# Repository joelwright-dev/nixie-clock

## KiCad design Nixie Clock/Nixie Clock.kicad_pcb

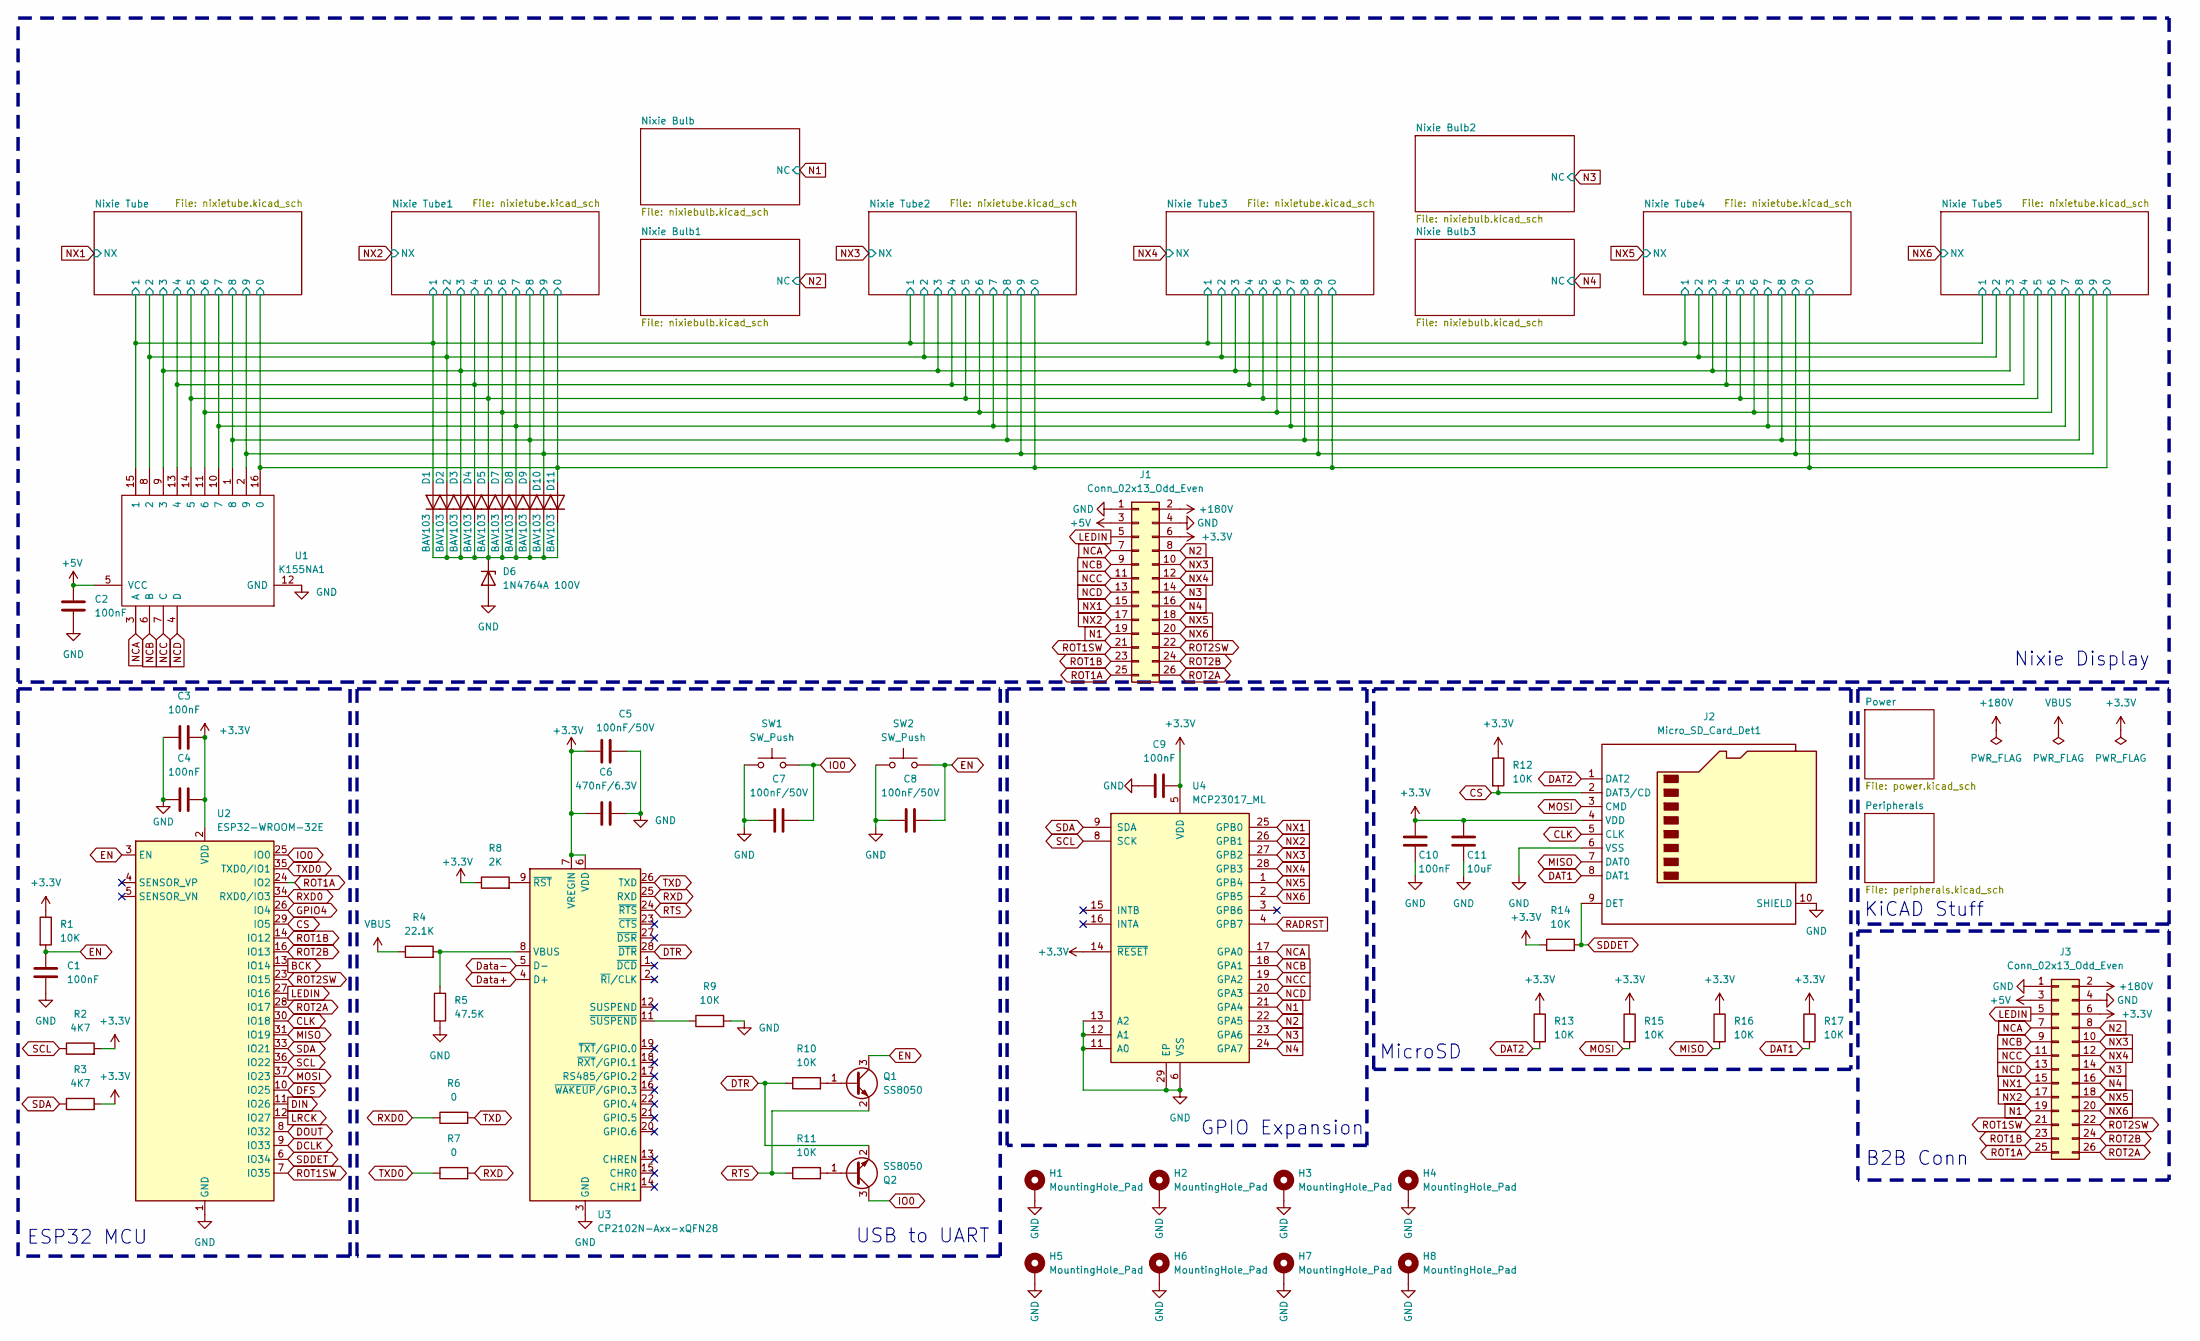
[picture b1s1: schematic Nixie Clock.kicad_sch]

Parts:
C1, C2, C3, C4, C9, C10: 100nF; C_0603_1608Metric
C5, C7, C8: 100nF/50V; C_0603_1608Metric
C6: 470nF/6.3V; C_0603_1608Metric
C11: 10uF; C_0603_1608Metric
D1, D2, D3, D4, D5, D7, D8, D9, D10, D11: BAV103; D_MiniMELF
D6: 1N4764A 100V; D_DO-41_SOD81_P7.62mm_Horizontal
H1, H2, H3, H4, H5, H6, H7, H8: MountingHole_Pad; MountingHole_3.2mm_M3_Pad_Via
J1: Conn_02x13_Odd_Even; PinHeader_2x13_P2.54mm_Vertical
J2: Micro_SD_Card_Det1; microSD_HC_Hirose_DM3AT-SF-PEJM5
J3: Conn_02x13_Odd_Even; PinSocket_2x13_P2.54mm_Vertical
Q1, Q2: SS8050; SOT-23
R1, R9, R10, R11, R12, R13, R14, R15, R16, R17: 10K; R_0603_1608Metric
R2, R3: 4K7; R_0603_1608Metric
R4: 22.1K; R_0603_1608Metric
R5: 47.5K; R_0603_1608Metric
R6, R7: 0; R_0603_1608Metric
R8: 2K; R_0603_1608Metric
SW1, SW2: SW_Push; SW_Push_SPST_NO_Alps_SKRK
U1: K155NA1; DIP-16_W7.62mm
U2: ESP32-WROOM-32E; ESP32-WROOM-32D
U3: CP2102N-Axx-xQFN28; QFN-28-1EP_5x5mm_P0.5mm_EP3.35x3.35mm
U4: MCP23017_ML; QFN-28-1EP_6x6mm_P0.65mm_EP4.25x4.25mm

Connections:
+3.3V: C3.2, C4.2, C5.1, C6.1, C9.2, C10.1, C11.1, J1.6, J2.4 (VDD), J3.6, R1.1, R2.2, R3.2, R8.1, R12.1, R13.1, R14.1, R15.1, R16.1, R17.1, U2.2 (VDD), U3.6 (VDD), U3.7 (VREGIN), U4.5 (VDD), U4.14 (~RESET); also elsewhere on the board
+5V: C2.1, J1.3, J3.3, U1.5 (VCC); also elsewhere on the board
+180V: J1.2, J3.2; also elsewhere on the board
/Nixie Tube/0: D11.2 (A), U1.16 (0); also elsewhere on the board
/Nixie Tube/1: D1.2 (A), U1.15 (1); also elsewhere on the board
/Nixie Tube/2: D2.2 (A), U1.8 (2); also elsewhere on the board
/Nixie Tube/3: D3.2 (A), U1.9 (3); also elsewhere on the board
/Nixie Tube/4: D4.2 (A), U1.13 (4); also elsewhere on the board
/Nixie Tube/5: D5.2 (A), U1.14 (5); also elsewhere on the board
/Nixie Tube/6: D7.2 (A), U1.11 (6); also elsewhere on the board
/Nixie Tube/7: D8.2 (A), U1.10 (7); also elsewhere on the board
/Nixie Tube/8: D9.2 (A), U1.1 (8); also elsewhere on the board
/Nixie Tube/9: D10.2 (A), U1.2 (9); also elsewhere on the board
BCK: U2.13 (IO14); also elsewhere on the board
CLK: J2.5 (CLK), U2.30 (IO18)
CS: J2.2 (DAT3/CD), R12.2, U2.29 (IO5)
DAT1: J2.8 (DAT1), R17.2
DAT2: J2.1 (DAT2), R13.2
DCLK: U2.9 (IO33); also elsewhere on the board
DFS: U2.10 (IO25); also elsewhere on the board
DIN: U2.11 (IO26); also elsewhere on the board
DOUT: U2.8 (IO32); also elsewhere on the board
DTR: Q2.2 (E), R10.1, U3.28 (~DTR)
Data+: U3.4 (D+); also elsewhere on the board
Data-: U3.5 (D-); also elsewhere on the board
EN: C1.1, C8.2, Q1.3 (C), R1.2, SW2.2, U2.3 (EN)
GND: C1.2, C2.2, C3.1, C4.1, C5.2, C6.2, C7.1, C8.1, C9.1, C10.2, C11.2, D6.2 (A), H1.1, H2.1, H3.1, H4.1, H5.1, H6.1, H7.1, H8.1, J1.1, J1.4, J2.6 (VSS), J2.10 (SHIELD), J3.1, J3.4, R5.2, R9.2, SW1.1, SW2.1, U1.12 (GND), U2.1 (GND), U2.15 (GND), U2.38 (GND), U2.39 (GND), U3.3 (GND), U3.29 (GND), U4.6 (VSS), U4.11 (A0), U4.12 (A1), U4.13 (A2), U4.29 (EP); also elsewhere on the board
GPIO4: U2.26 (IO4); also elsewhere on the board
IO0: C7.2, Q2.3 (C), SW1.2, U2.25 (IO0)
LEDIN: J1.5, J3.5, U2.27 (IO16); also elsewhere on the board
LRCK: U2.12 (IO27); also elsewhere on the board
MISO: J2.7 (DAT0), R16.2, U2.31 (IO19)
MOSI: J2.3 (CMD), R15.2, U2.37 (IO23)
N1: J1.19, J3.19, U4.21 (GPA4); also elsewhere on the board
N2: J1.8, J3.8, U4.22 (GPA5); also elsewhere on the board
N3: J1.14, J3.14, U4.23 (GPA6); also elsewhere on the board
N4: J1.16, J3.16, U4.24 (GPA7); also elsewhere on the board
NCA: J1.7, J3.7, U1.3 (A), U4.17 (GPA0)
NCB: J1.9, J3.9, U1.6 (B), U4.18 (GPA1)
NCC: J1.11, J3.11, U1.7 (C), U4.19 (GPA2)
NCD: J1.13, J3.13, U1.4 (D), U4.20 (GPA3)
NX1: J1.15, J3.15, U4.25 (GPB0); also elsewhere on the board
NX2: J1.17, J3.17, U4.26 (GPB1); also elsewhere on the board
NX3: J1.10, J3.10, U4.27 (GPB2); also elsewhere on the board
NX4: J1.12, J3.12, U4.28 (GPB3); also elsewhere on the board
NX5: J1.18, J3.18, U4.1 (GPB4); also elsewhere on the board
NX6: J1.20, J3.20, U4.2 (GPB5); also elsewhere on the board
unnamed: D1.1 (K), D2.1 (K), D3.1 (K), D4.1 (K), D5.1 (K), D6.1 (K), D7.1 (K), D8.1 (K), D9.1 (K), D10.1 (K), D11.1 (K)
unnamed: Q1.1 (B), R10.2
unnamed: Q2.1 (B), R11.2
unnamed: R4.2, R5.1, U3.8 (VBUS)
unnamed: R8.2, U3.9 (~RST)
unnamed: R9.1, U3.11 (~SUSPEND)
RADRST: U4.4 (GPB7); also elsewhere on the board
ROT1A: J1.25, J3.25, U2.24 (IO2); also elsewhere on the board
ROT1B: J1.23, J3.23, U2.14 (IO12); also elsewhere on the board
ROT1SW: J1.21, J3.21, U2.7 (IO35); also elsewhere on the board
ROT2A: J1.26, J3.26, U2.28 (IO17); also elsewhere on the board
ROT2B: J1.24, J3.24, U2.16 (IO13); also elsewhere on the board
ROT2SW: J1.22, J3.22, U2.23 (IO15); also elsewhere on the board
RTS: Q1.2 (E), R11.1, U3.24 (~RTS)
RXD: R7.2, U3.25 (RXD)
RXD0: R6.1, U2.34 (RXD0/IO3)
SCL: R2.1, U2.36 (IO22), U4.8 (SCK); also elsewhere on the board
SDA: R3.1, U2.33 (IO21), U4.9 (SDA); also elsewhere on the board
SDDET: J2.9 (DET), R14.2, U2.6 (IO34)
TXD: R6.2, U3.26 (TXD)
TXD0: R7.1, U2.35 (TXD0/IO1)
VBUS: R4.1; also elsewhere on the board

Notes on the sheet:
MicroSD
KiCAD Stuff
USB to UART
Nixie Display
B2B Conn
ESP32 MCU
GPIO Expansion

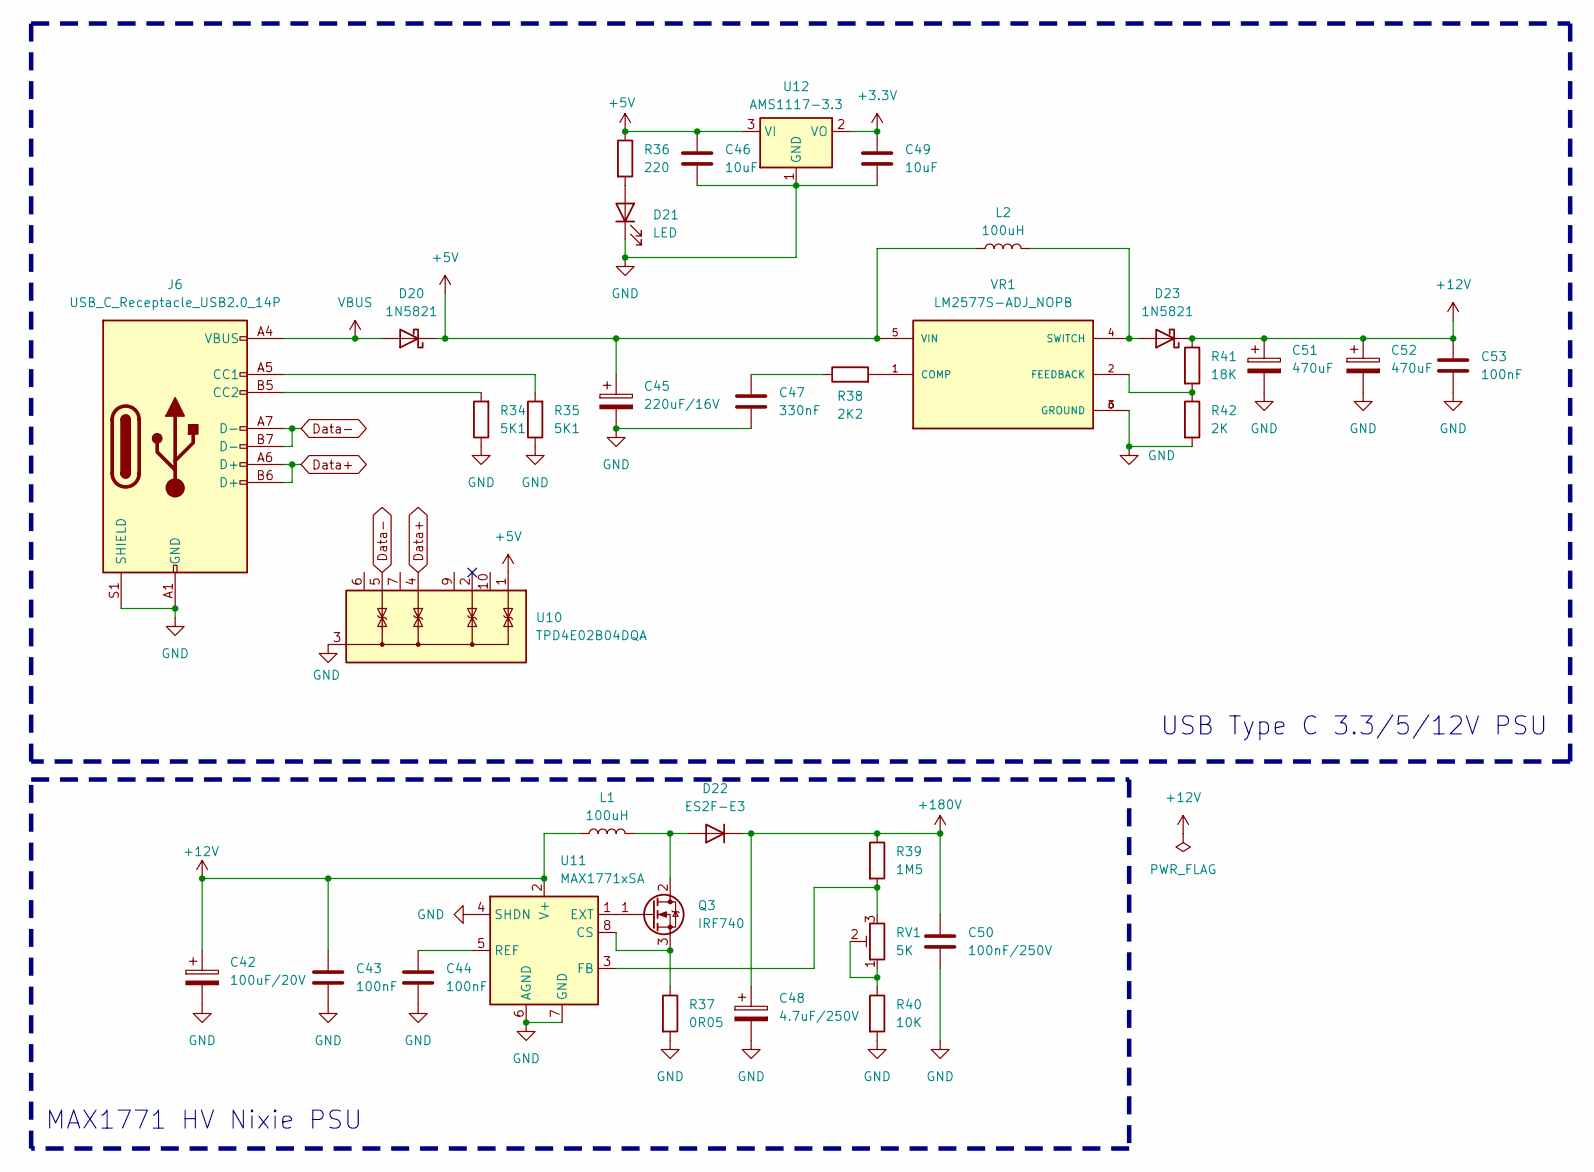
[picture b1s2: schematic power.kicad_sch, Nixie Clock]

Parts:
C42: 100uF/20V; CP_Elec_6.3x7.7
C43, C44, C53: 100nF; C_0603_1608Metric
C45: 220uF/16V; CP_Elec_10x10
C46, C49: 10uF; C_0603_1608Metric
C47: 330nF; C_0603_1608Metric
C48: 4.7uF/250V; CP_Elec_8x10.5
C50: 100nF/250V; C_0603_1608Metric
C51, C52: 470uF; CP_Elec_10x10.5
D20, D23: 1N5821; D_DO-201AD_P12.70mm_Horizontal
D21: LED; LED_0201_0603Metric
D22: ES2F-E3; D_SMB
J6: USB_C_Receptacle_USB2.0_14P; USB_C_Receptacle_G-Switch_GT-USB-7051x
L1, L2: 100uH; L_12x12mm_H8mm
Q3: IRF740; TO-220-3_Horizontal_TabUp
R34, R35: 5K1; R_0603_1608Metric
R36: 220; R_0603_1608Metric
R37: 0R05; R_0603_1608Metric
R38: 2K2; R_0603_1608Metric
R39: 1M5; R_0603_1608Metric
R40: 10K; R_0603_1608Metric
R41: 18K; R_0603_1608Metric
R42: 2K; R_0603_1608Metric
RV1: 5K; Potentiometer_Bourns_3296W_Vertical
U10: TPD4E02B04DQA; USON-10_2.5x1.0mm_P0.5mm
U11: MAX1771xSA; SO-8_3.9x4.9mm_P1.27mm
U12: AMS1117-3.3; SOT-223-3_TabPin2
VR1: LM2577S-ADJ_NOPB; VREG_LM2577S-ADJ_NOPB; PARTREV D

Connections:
+3.3V: C49.1, U12.2 (VO); also elsewhere on the board
+5V: C45.1, C46.1, D20.1 (K), L2.1, R36.1, U10.1 (IO1), U12.3 (VI), VR1.5 (VIN); also elsewhere on the board
+12V: C42.1, C43.1, C51.1, C52.1, C53.1, D23.1 (K), L1.1, R41.1, U11.2 (V+)
+180V: C48.1, C50.1, D22.1 (K), R39.1; also elsewhere on the board
Data+: J6.A6 (D+), J6.B6 (D+), U10.4 (IO3); also elsewhere on the board
Data-: J6.A7 (D-), J6.B7 (D-), U10.5 (IO4); also elsewhere on the board
GND: C42.2, C43.2, C44.2, C45.2, C46.2, C47.2, C48.2, C49.2, C50.2, C51.2, C52.2, C53.2, D21.1 (K), J6.A1 (GND), J6.A12 (GND), J6.B1 (GND), J6.B12 (GND), J6.S1 (SHIELD), R34.1, R35.1, R37.2, R40.2, R42.2, U10.3 (G), U10.8 (G), U11.4 (SHDN), U11.6 (AGND), U11.7 (GND), U12.1 (GND), VR1.3 (GROUND), VR1.6 (GROUND); also elsewhere on the board
unnamed: C47.1, R38.1
unnamed: D21.2 (A), R36.2
unnamed: D22.2 (A), L1.2, Q3.2 (D)
unnamed: D23.2 (A), L2.2, VR1.4 (SWITCH)
unnamed: J6.A5 (CC1), R35.2
unnamed: J6.B5 (CC2), R34.2
unnamed: Q3.1 (G), U11.1 (EXT)
unnamed: Q3.3 (S), R37.1, U11.8 (CS)
unnamed: R40.1, RV1.1, RV1.2
unnamed: R39.2, RV1.3, U11.3 (FB)
unnamed: C44.1, U11.5 (REF)
unnamed: R38.2, VR1.1 (COMP)
unnamed: R41.2, R42.1, VR1.2 (FEEDBACK)
VBUS: D20.2 (A), J6.A4 (VBUS), J6.A9 (VBUS), J6.B4 (VBUS), J6.B9 (VBUS); also elsewhere on the board

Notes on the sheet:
USB Type C 3.3/5/12V PSU
MAX1771 HV Nixie PSU

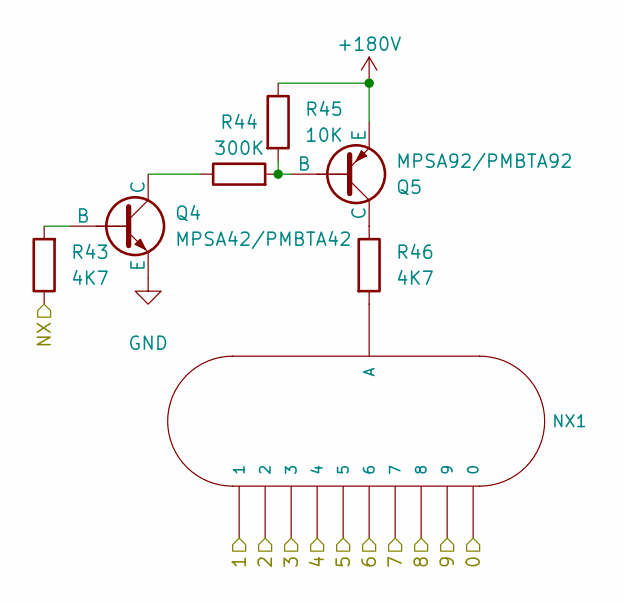
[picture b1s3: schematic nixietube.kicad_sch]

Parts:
NX1: IN-12A; IN-12-DSUB-NOHOLE
Q4: MPSA42/PMBTA42; SOT-23
Q5: MPSA92/PMBTA92; SOT-23
R43, R46: 4K7; R_0603_1608Metric
R44: 300K; R_0603_1608Metric
R45: 10K; R_0603_1608Metric

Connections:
+180V: Q5.3 (E), R45.1; also elsewhere on the board
/Nixie Tube/0: NX1.0; also elsewhere on the board
/Nixie Tube/1: NX1.1; also elsewhere on the board
/Nixie Tube/2: NX1.2; also elsewhere on the board
/Nixie Tube/3: NX1.3; also elsewhere on the board
/Nixie Tube/4: NX1.4; also elsewhere on the board
/Nixie Tube/5: NX1.5; also elsewhere on the board
/Nixie Tube/6: NX1.6; also elsewhere on the board
/Nixie Tube/7: NX1.7; also elsewhere on the board
/Nixie Tube/8: NX1.8; also elsewhere on the board
/Nixie Tube/9: NX1.9; also elsewhere on the board
GND: Q4.3 (E); also elsewhere on the board
NX1: R43.1; also elsewhere on the board
unnamed: NX1.A, R46.2
unnamed: Q4.2 (B), R43.2
unnamed: Q4.1 (C), R44.1
unnamed: Q5.2 (B), R44.2, R45.2
unnamed: Q5.1 (C), R46.1

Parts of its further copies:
NX2, NX3, NX4, NX5, NX6: IN-12A; IN-12-DSUB-NOHOLE
Q6, Q8, Q10, Q12, Q14: MPSA42/PMBTA42; SOT-23
Q7, Q9, Q11, Q13, Q15: MPSA92/PMBTA92; SOT-23
R47, R50, R51, R54, R55, R58, R59, R62, R63, R66: 4K7; R_0603_1608Metric
R48, R52, R56, R60, R64: 300K; R_0603_1608Metric
R49, R53, R57, R61, R65: 10K; R_0603_1608Metric

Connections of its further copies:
+180V: Q7.3 (E), Q9.3 (E), Q11.3 (E), Q13.3 (E), Q15.3 (E), R49.1, R53.1, R57.1, R61.1, R65.1; also elsewhere on the board
/Nixie Tube/0: NX2.0, NX3.0, NX4.0, NX5.0, NX6.0; also elsewhere on the board
/Nixie Tube/1: NX2.1, NX3.1, NX4.1, NX5.1, NX6.1; also elsewhere on the board
/Nixie Tube/2: NX2.2, NX3.2, NX4.2, NX5.2, NX6.2; also elsewhere on the board
/Nixie Tube/3: NX2.3, NX3.3, NX4.3, NX5.3, NX6.3; also elsewhere on the board
/Nixie Tube/4: NX2.4, NX3.4, NX4.4, NX5.4, NX6.4; also elsewhere on the board
/Nixie Tube/5: NX2.5, NX3.5, NX4.5, NX5.5, NX6.5; also elsewhere on the board
/Nixie Tube/6: NX2.6, NX3.6, NX4.6, NX5.6, NX6.6; also elsewhere on the board
/Nixie Tube/7: NX2.7, NX3.7, NX4.7, NX5.7, NX6.7; also elsewhere on the board
/Nixie Tube/8: NX2.8, NX3.8, NX4.8, NX5.8, NX6.8; also elsewhere on the board
/Nixie Tube/9: NX2.9, NX3.9, NX4.9, NX5.9, NX6.9; also elsewhere on the board
GND: Q6.3 (E), Q8.3 (E), Q10.3 (E), Q12.3 (E), Q14.3 (E); also elsewhere on the board
NX2: R47.1; also elsewhere on the board
NX3: R51.1; also elsewhere on the board
NX4: R55.1; also elsewhere on the board
NX5: R59.1; also elsewhere on the board
NX6: R63.1; also elsewhere on the board
unnamed: NX2.A, R50.2
unnamed: NX3.A, R54.2
unnamed: NX4.A, R58.2
unnamed: NX5.A, R62.2
unnamed: NX6.A, R66.2
unnamed: Q6.2 (B), R47.2
unnamed: Q6.1 (C), R48.1
unnamed: Q7.2 (B), R48.2, R49.2
unnamed: Q7.1 (C), R50.1
unnamed: Q8.2 (B), R51.2
unnamed: Q8.1 (C), R52.1
unnamed: Q9.2 (B), R52.2, R53.2
unnamed: Q9.1 (C), R54.1
unnamed: Q10.2 (B), R55.2
unnamed: Q10.1 (C), R56.1
unnamed: Q11.2 (B), R56.2, R57.2
unnamed: Q11.1 (C), R58.1
unnamed: Q12.2 (B), R59.2
unnamed: Q12.1 (C), R60.1
unnamed: Q13.2 (B), R60.2, R61.2
unnamed: Q13.1 (C), R62.1
unnamed: Q14.2 (B), R63.2
unnamed: Q14.1 (C), R64.1
unnamed: Q15.2 (B), R64.2, R65.2
unnamed: Q15.1 (C), R66.1

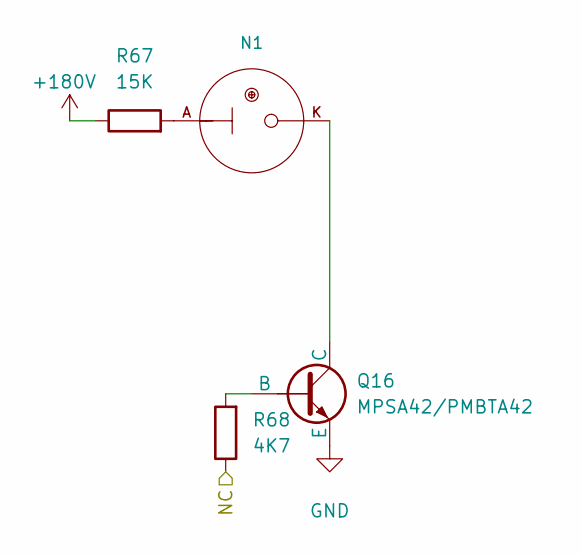
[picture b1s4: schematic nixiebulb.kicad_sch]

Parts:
N1: IN-6
Q16: MPSA42/PMBTA42; SOT-23
R67: 15K; R_0603_1608Metric
R68: 4K7; R_0603_1608Metric

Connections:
+180V: R67.1; also elsewhere on the board
GND: Q16.3 (E); also elsewhere on the board
N1: R68.1; also elsewhere on the board
unnamed: N1.A, R67.2
unnamed: Q16.2 (B), R68.2
unnamed: N1.K, Q16.1 (C)

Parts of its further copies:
N2, N3, N4: IN-6
Q17, Q18, Q19: MPSA42/PMBTA42; SOT-23
R69, R71, R73: 15K; R_0603_1608Metric
R70, R72, R74: 4K7; R_0603_1608Metric

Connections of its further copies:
+180V: R69.1, R71.1, R73.1; also elsewhere on the board
GND: Q17.3 (E), Q18.3 (E), Q19.3 (E); also elsewhere on the board
N2: R70.1; also elsewhere on the board
N3: R72.1; also elsewhere on the board
N4: R74.1; also elsewhere on the board
unnamed: N2.A, R69.2
unnamed: N3.A, R71.2
unnamed: N4.A, R73.2
unnamed: Q17.2 (B), R70.2
unnamed: N2.K, Q17.1 (C)
unnamed: Q18.2 (B), R72.2
unnamed: N3.K, Q18.1 (C)
unnamed: Q19.2 (B), R74.2
unnamed: N4.K, Q19.1 (C)

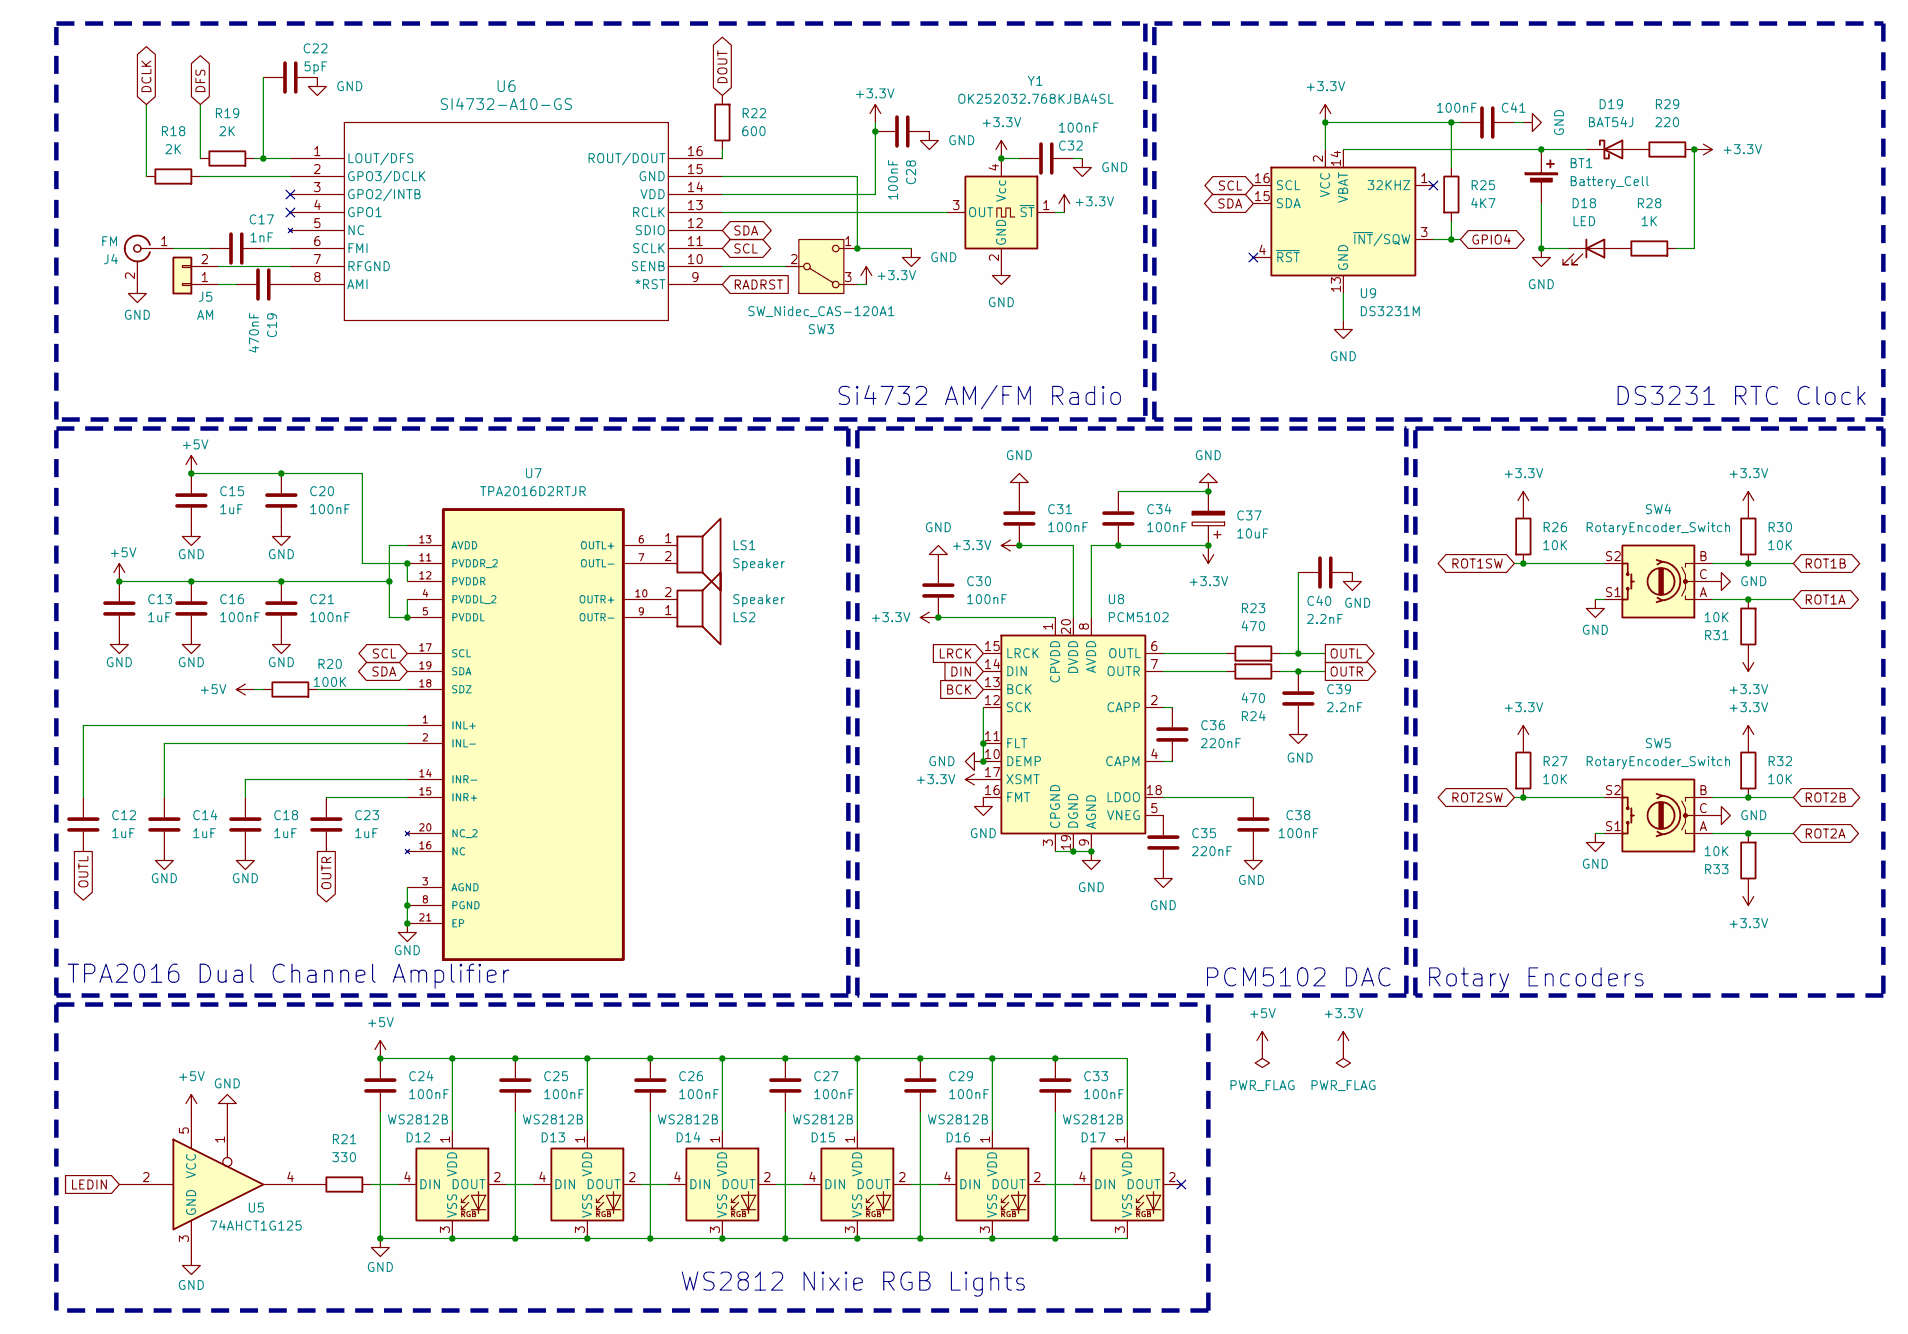
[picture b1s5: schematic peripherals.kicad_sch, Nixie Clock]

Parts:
BT1: Battery_Cell; BatteryHolder_Keystone_1060_1x2032
C12, C13, C14, C15, C18, C23: 1uF; C_0603_1608Metric
C16, C20, C21, C24, C25, C26, C27, C28, C29, C30, C31, C32, C33, C34, C38, C41: 100nF; C_0603_1608Metric
C17: 1nF; C_0603_1608Metric
C19: 470nF; C_0603_1608Metric
C22: 5pF; C_0603_1608Metric
C35, C36: 220nF; C_0603_1608Metric
C37: 10uF; C_0603_1608Metric
C39, C40: 2.2nF; C_0603_1608Metric
D12, D13, D14, D15, D16, D17: WS2812B; LED_WS2812B_PLCC4_5.0x5.0mm_P3.2mm
D18: LED; LED_0201_0603Metric
D19: BAT54J; D_SOD-323F
J4: FM; SMA_Amphenol_901-144_Vertical
J5: AM; JST_XH_B2B-XH-A_1x02_P2.50mm_Vertical
LS1, LS2: Speaker; JST_XH_B2B-XH-A_1x02_P2.50mm_Vertical
R18, R19: 2K; R_0603_1608Metric
R20: 100K; R_0603_1608Metric
R21: 330; R_0603_1608Metric
R22: 600; R_0603_1608Metric
R23, R24: 470; R_0603_1608Metric
R25: 4K7; R_0603_1608Metric
R26, R27, R30, R31, R32, R33: 10K; R_0603_1608Metric
R28: 1K; R_0603_1608Metric
R29: 220; R_0603_1608Metric
SW3: SW_Nidec_CAS-120A1; Nidec_Copal_CAS-120A
SW4, SW5: RotaryEncoder_Switch; RotaryEncoder_Alps_EC11E-Switch_Vertical_H20mm
U5: 74AHCT1G125; SOT-23-5
U6: SI4732-A10-GS; SOIC_A10-GS_SIL
U7: TPA2016D2RTJR; QFN50P400X400X80-21N; MPN TPA2016D2RTJR
U8: PCM5102; TSSOP-20_4.4x6.5mm_P0.65mm
U9: DS3231M; SOIC-16W_7.5x10.3mm_P1.27mm
Y1: OK252032.768KJBA4SL; Oscillator_SMD_SeikoEpson_SG210-4Pin_2.5x2.0mm

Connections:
+3.3V: C28.2, C30.1, C31.1, C32.2, C34.1, C37.1, C41.2, R25.1, R26.1, R27.1, R28.2, R29.2, R30.1, R31.1, R32.1, R33.1, SW3.3 (A), U6.14 (VDD), U8.1 (CPVDD), U8.8 (AVDD), U8.17 (XSMT), U8.20 (DVDD), U9.2 (VCC), Y1.1 (~ST), Y1.4 (Vcc); also elsewhere on the board
+5V: C13.2, C15.2, C16.2, C20.2, C21.2, C24.1, C25.1, C26.1, C27.1, C29.1, C33.1, D12.1 (VDD), D13.1 (VDD), D14.1 (VDD), D15.1 (VDD), D16.1 (VDD), D17.1 (VDD), R20.1, U5.5 (VCC), U7.4 (PVDDL_2), U7.5 (PVDDL), U7.11 (PVDDR_2), U7.12 (PVDDR), U7.13 (AVDD); also elsewhere on the board
BCK: U8.13 (BCK); also elsewhere on the board
DCLK: R18.1; also elsewhere on the board
DFS: R19.1; also elsewhere on the board
DIN: U8.14 (DIN); also elsewhere on the board
DOUT: R22.2; also elsewhere on the board
GND: BT1.2 (-), C13.1, C14.1, C15.1, C16.1, C18.1, C20.1, C21.1, C22.1, C24.2, C25.2, C26.2, C27.2, C28.1, C29.2, C30.2, C31.2, C32.1, C33.2, C34.2, C35.2, C37.2, C38.2, C39.2, C40.1, C41.1, D12.3 (VSS), D13.3 (VSS), D14.3 (VSS), D15.3 (VSS), D16.3 (VSS), D17.3 (VSS), D18.1 (K), J4.2 (Ext), SW3.1 (C), SW4.C, SW4.S1, SW5.C, SW5.S1, U5.1, U5.3 (GND), U6.15 (GND), U7.3 (AGND), U7.8 (PGND), U7.21 (EP), U8.3 (CPGND), U8.9 (AGND), U8.10 (DEMP), U8.11 (FLT), U8.12 (SCK), U8.16 (FMT), U8.19 (DGND), U9.5 (GND), U9.6 (GND), U9.7 (GND), U9.8 (GND), U9.9 (GND), U9.10 (GND), U9.11 (GND), U9.12 (GND), U9.13 (GND), Y1.2 (GND); also elsewhere on the board
GPIO4: R25.2, U9.3 (~INT/SQW); also elsewhere on the board
LEDIN: U5.2; also elsewhere on the board
LRCK: U8.15 (LRCK); also elsewhere on the board
unnamed: BT1.1 (+), D19.1 (K), U9.14 (VBAT)
unnamed: D12.4 (DIN), R21.2
unnamed: D12.2 (DOUT), D13.4 (DIN)
unnamed: D13.2 (DOUT), D14.4 (DIN)
unnamed: D14.2 (DOUT), D15.4 (DIN)
unnamed: D15.2 (DOUT), D16.4 (DIN)
unnamed: D16.2 (DOUT), D17.4 (DIN)
unnamed: D18.2 (A), R28.1
unnamed: D19.2 (A), R29.1
unnamed: C17.2, J4.1 (In)
unnamed: C19.2, J5.1
unnamed: J5.2, U6.7 (RFGND)
unnamed: R21.1, U5.4
unnamed: SW3.2 (B), U6.10 (SENB)
unnamed: C19.1, U6.8 (AMI)
unnamed: C17.1, U6.6 (FMI)
unnamed: R18.2, U6.2 (GPO3/DCLK)
unnamed: C22.2, R19.2, U6.1 (LOUT/DFS)
unnamed: U6.13 (RCLK), Y1.3 (OUT)
unnamed: R22.1, U6.16 (ROUT/DOUT)
unnamed: C12.2, U7.1 (INL+)
unnamed: C14.2, U7.2 (INL-)
unnamed: C23.2, U7.15 (INR+)
unnamed: C18.2, U7.14 (INR-)
unnamed: LS1.1, U7.6 (OUTL+)
unnamed: LS1.2, U7.7 (OUTL-)
unnamed: LS2.2, U7.10 (OUTR+)
unnamed: LS2.1, U7.9 (OUTR-)
unnamed: R20.2, U7.18 (SDZ)
unnamed: C36.2, U8.4 (CAPM)
unnamed: C36.1, U8.2 (CAPP)
unnamed: C38.1, U8.18 (LDOO)
unnamed: R23.1, U8.6 (OUTL)
unnamed: R24.2, U8.7 (OUTR)
unnamed: C35.1, U8.5 (VNEG)
OUTL: C12.1, C40.2, R23.2
OUTR: C23.1, C39.1, R24.1
RADRST: U6.9 (*RST); also elsewhere on the board
ROT1A: R31.2, SW4.A; also elsewhere on the board
ROT1B: R30.2, SW4.B; also elsewhere on the board
ROT1SW: R26.2, SW4.S2; also elsewhere on the board
ROT2A: R33.2, SW5.A; also elsewhere on the board
ROT2B: R32.2, SW5.B; also elsewhere on the board
ROT2SW: R27.2, SW5.S2; also elsewhere on the board
SCL: U6.11 (SCLK), U7.17 (SCL), U9.16 (SCL); also elsewhere on the board
SDA: U6.12 (SDIO), U7.19 (SDA), U9.15 (SDA); also elsewhere on the board

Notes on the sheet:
Si4732 AM/FM Radio
TPA2016 Dual Channel Amplifier
PCM5102 DAC
DS3231 RTC Clock
WS2812 Nixie RGB Lights
Rotary Encoders

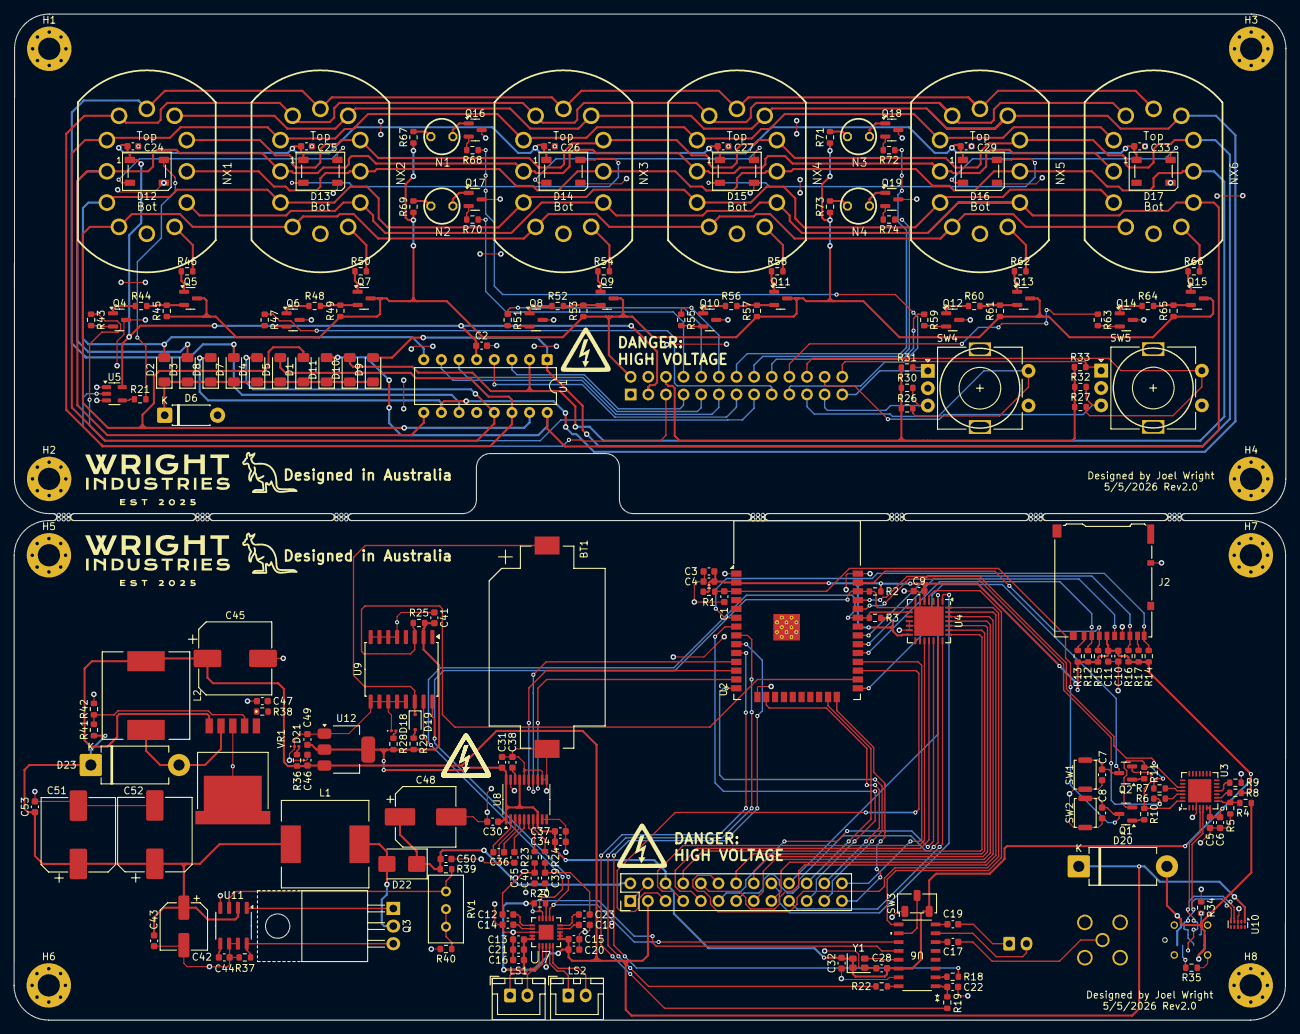
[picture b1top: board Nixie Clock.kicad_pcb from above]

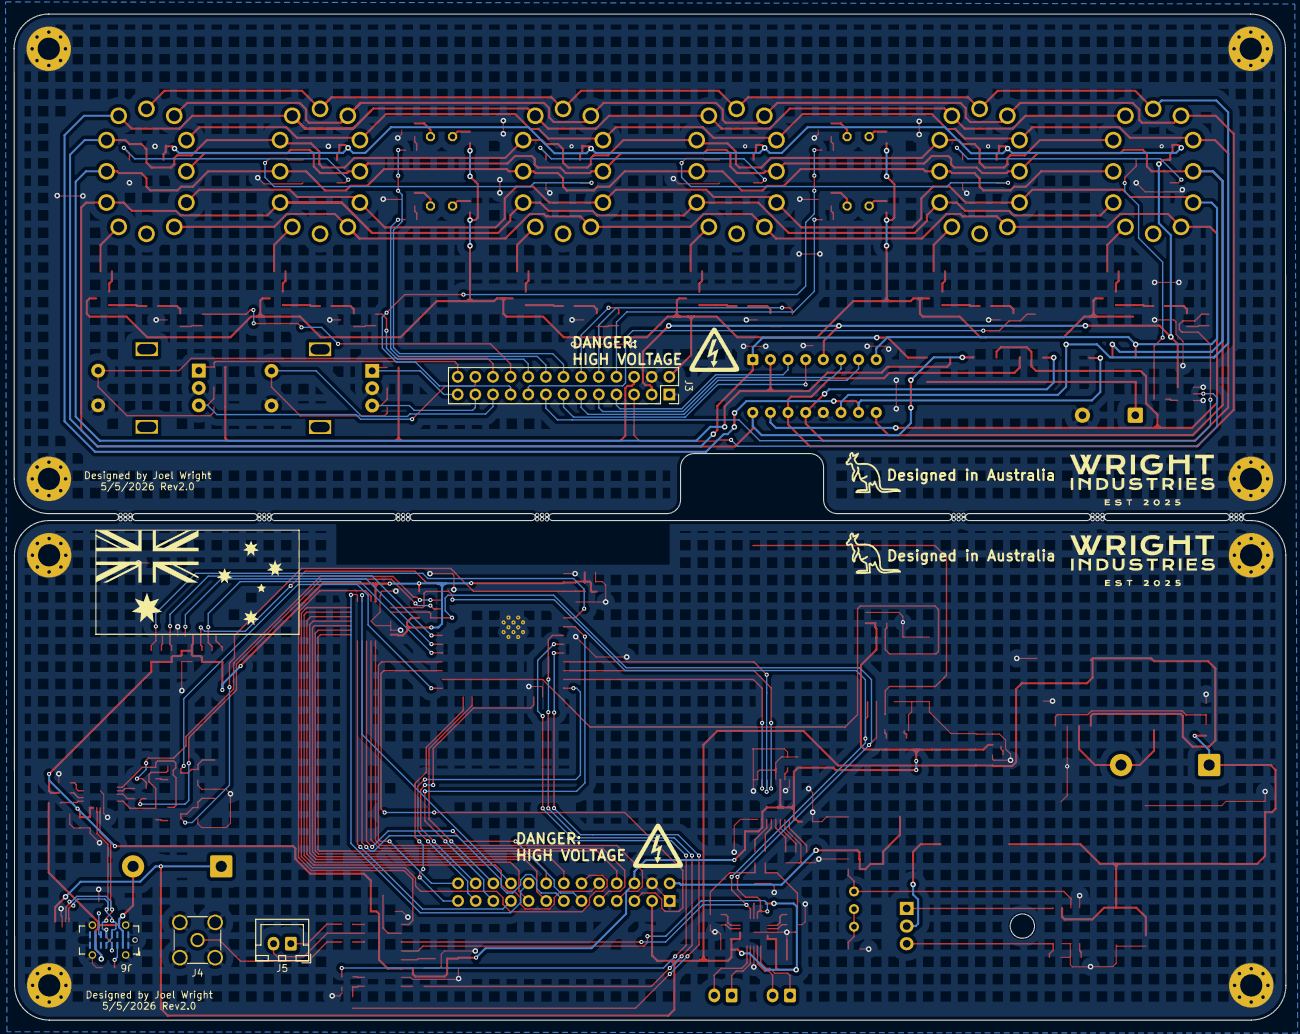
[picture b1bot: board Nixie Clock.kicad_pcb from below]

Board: 2 copper layers, 183.2 x 144.9 mm, 225 parts (4 on the bottom side), 162 nets.

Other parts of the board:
mouse-bite-1mm-3mm, mouse-bite-1mm-3mm#2, mouse-bite-1mm-3mm#3, mouse-bite-1mm-3mm#4, mouse-bite-1mm-3mm#5, mouse-bite-1mm-3mm#6, mouse-bite-1mm-3mm#7: VAL**; mouse-bite-1mm-3mm

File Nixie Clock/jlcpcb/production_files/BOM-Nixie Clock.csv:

Comment,Designator,Footprint,LCSC,Quantity
0,"R6,R7",R_0603_1608Metric,C21189,2
0R05,R37,R_0603_1608Metric,C14709,1
100K,R20,R_0603_1608Metric,C25803,1
100nF,"C1,C10,C16,C2,C20,C21,C24,C25,C26,C27,C28,C29,C3,C30,C31,C32,C33,C34,C38,C4,C41,C43,C44,C53,C9",C_0603_1608Metric,C14663,25
100nF/250V,C50,C_1206_3216Metric,C22374889,1
100nF/50V,"C5,C7,C8",C_0603_1608Metric,C14663,3
100uF/20V,C42,CP_Elec_6.3x7.7,C3338,1
100uH,"L1,L2",L_12x12mm_H8mm,C6463690,2
10K,"R1,R10,R11,R12,R13,R14,R15,R16,R17,R26,R27,R30,R31,R32,R33,R40,R45,R49,R53,R57,R61,R65,R9",R_0603_1608Metric,C25804,23
10uF,"C11,C37,C46,C49",C_0603_1608Metric,C96446,4
15K,"R67,R69,R71,R73",R_0603_1608Metric,C22809,4
18K,R41,R_0603_1608Metric,C25810,1
1K,R28,R_0603_1608Metric,C21190,1
1M5,R39,R_0603_1608Metric,C4172,1
1N4764A 100V,D6,D_DO-41_SOD81_P7.62mm_Horizontal,C2764506,1
1N5821,"D20,D23",D_DO-201AD_P12.70mm_Horizontal,C9119,2
1nF,C17,C_0603_1608Metric,C1588,1
1uF,"C12,C13,C14,C15,C18,C23",C_0603_1608Metric,C15849,6
2.2nF,"C39,C40",C_0603_1608Metric,C1604,2
22.1K,R4,R_0603_1608Metric,C2960862,1
220,"R29,R36",R_0603_1608Metric,C22962,2
220nF,"C35,C36",C_0603_1608Metric,C21120,2
220uF/16V,C45,CP_Elec_10x10,C3358,1
2K,"R18,R19,R42,R8",R_0603_1608Metric,C22975,4
2K2,R38,R_0603_1608Metric,C4190,1
300K,"R44,R48,R52,R56,R60,R64",R_0603_1608Metric,C23024,6
330,R21,R_0603_1608Metric,C23138,1
330nF,C47,C_0603_1608Metric,C1615,1
4.7uF/250V,C48,CP_Elec_8x10.5,C88702,1
47.5K,R5,R_0603_1608Metric,C2933225,1
470,"R23,R24",R_0603_1608Metric,C23179,2
470nF,C19,C_0603_1608Metric,C1623,1
470nF/6.3V,C6,C_0603_1608Metric,C1623,1
470uF,"C51,C52",CP_Elec_10x10.5,C3350,2
4K7,"R2,R25,R3,R43,R46,R47,R50,R51,R54,R55,R58,R59,R62,R63,R66,R68,R70,R72,R74",R_0603_1608Metric,C23162,19
5K,RV1,Potentiometer_Bourns_3296W_Vertical,C60620,1
5K1,"R34,R35",R_0603_1608Metric,C23186,2
5pF,C22,C_0603_1608Metric,C1644,1
600,R22,R_0603_1608Metric,C1002,1
74AHCT1G125,U5,SOT-23-5,C20617903,1
AM,J5,JST_XH_B2B-XH-A_1x02_P2.50mm_Vertical,C158012,1
AMS1117-3.3,U12,SOT-223-3_TabPin2,C6186,1
BAT54J,D19,D_SOD-323F,C358488,1
BAV103,"D1,D10,D11,D2,D3,D4,D5,D7,D8,D9",D_MiniMELF,C5118933,10
Battery_Cell,BT1,BatteryHolder_Keystone_1060_1x2032,C70377,1
CP2102N-Axx-xQFN28,U3,QFN-28-1EP_5x5mm_P0.5mm_EP3.35x3.35mm,C964632,1
Conn_02x13_Odd_Even,J1,PinHeader_2x13_P2.54mm_Vertical,C2894974,1
Conn_02x13_Odd_Even,J3,PinSocket_2x13_P2.54mm_Vertical,C2897414,1
DS3231M,U9,SOIC-16W_7.5x10.3mm_P1.27mm,C37663,1
ES2F-E3,D22,D_SMB,C222525,1
ESP32-WROOM-32E,U2,ESP32-WROOM-32D,C5361945,1
FM,J4,SMA_Amphenol_901-144_Vertical,C22454024,1
IRF740,Q3,TO-220-3_Horizontal_TabUp,C2570,1
K155NA1,U1,DIP-16_W7.62mm,C146580,1
LED,"D18,D21",LED_0201_0603Metric,C5440629,2
LM2577S-ADJ_NOPB,VR1,VREG_LM2577S-ADJ_NOPB,C18221474,1
MAX1771xSA,U11,SO-8_3.9x4.9mm_P1.27mm,C407903,1
MCP23017_ML,U4,QFN-28-1EP_6x6mm_P0.65mm_EP4.25x4.25mm,C629439,1
MPSA42/PMBTA42,"Q10,Q12,Q14,Q16,Q17,Q18,Q19,Q4,Q6,Q8",SOT-23,C417384,10
MPSA92/PMBTA92,"Q11,Q13,Q15,Q5,Q7,Q9",SOT-23,C282560,6
Micro_SD_Card_Det1,J2,microSD_HC_Hirose_DM3AT-SF-PEJM5,C114218,1
OK252032.768KJBA4SL,Y1,Oscillator_SMD_SeikoEpson_SG210-4Pin_2.5x2.0mm,C669098,1
PCM5102,U8,TSSOP-20_4.4x6.5mm_P0.65mm,C107671,1
RotaryEncoder_Switch,"SW4,SW5",RotaryEncoder_Alps_EC11E-Switch_Vertical_H20mm,C370970,2
SI4732-A10-GS,U6,SOIC_A10-GS_SIL,C2155558,1
SS8050,"Q1,Q2",SOT-23,C2150,2
SW_Nidec_CAS-120A1,SW3,Nidec_Copal_CAS-120A,C22401620,1
SW_Push,"SW1,SW2",SW_Push_SPST_NO_Alps_SKRK,C202388,2
Speaker,"LS1,LS2",JST_XH_B2B-XH-A_1x02_P2.50mm_Vertical,C158012,2
TPA2016D2RTJR,U7,QFN50P400X400X80-21N,C412823,1
TPD4E02B04DQA,U10,USON-10_2.5x1.0mm_P0.5mm,C106794,1
USB_C_Receptacle_USB2.0_14P,J6,USB_C_Receptacle_G-Switch_GT-USB-7051x,C2843970,1
WS2812B,"D12,D13,D14,D15,D16,D17",LED_WS2812B_PLCC4_5.0x5.0mm_P3.2mm,C2761795,6
VAL**,mouse-bite-1mm-3mm,mouse-bite-1mm-3mm,,1

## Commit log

2026-05-05 PCB routed
2026-05-06 Update footprints
2026-05-07 Assign JLCPCB parts
2026-05-24 Rev2.1 depopulated R30 and R31 pullup resistors
2026-06-17 change R37 and R39 to higher rated resistors
2026-06-27 Add MAX3421 and CH334R for mass storage device capability
2026-06-27 Route PCB rev2.1
2026-06-27 Generated gerbers
2026-06-28 Add capacitor across R39 for filtering
